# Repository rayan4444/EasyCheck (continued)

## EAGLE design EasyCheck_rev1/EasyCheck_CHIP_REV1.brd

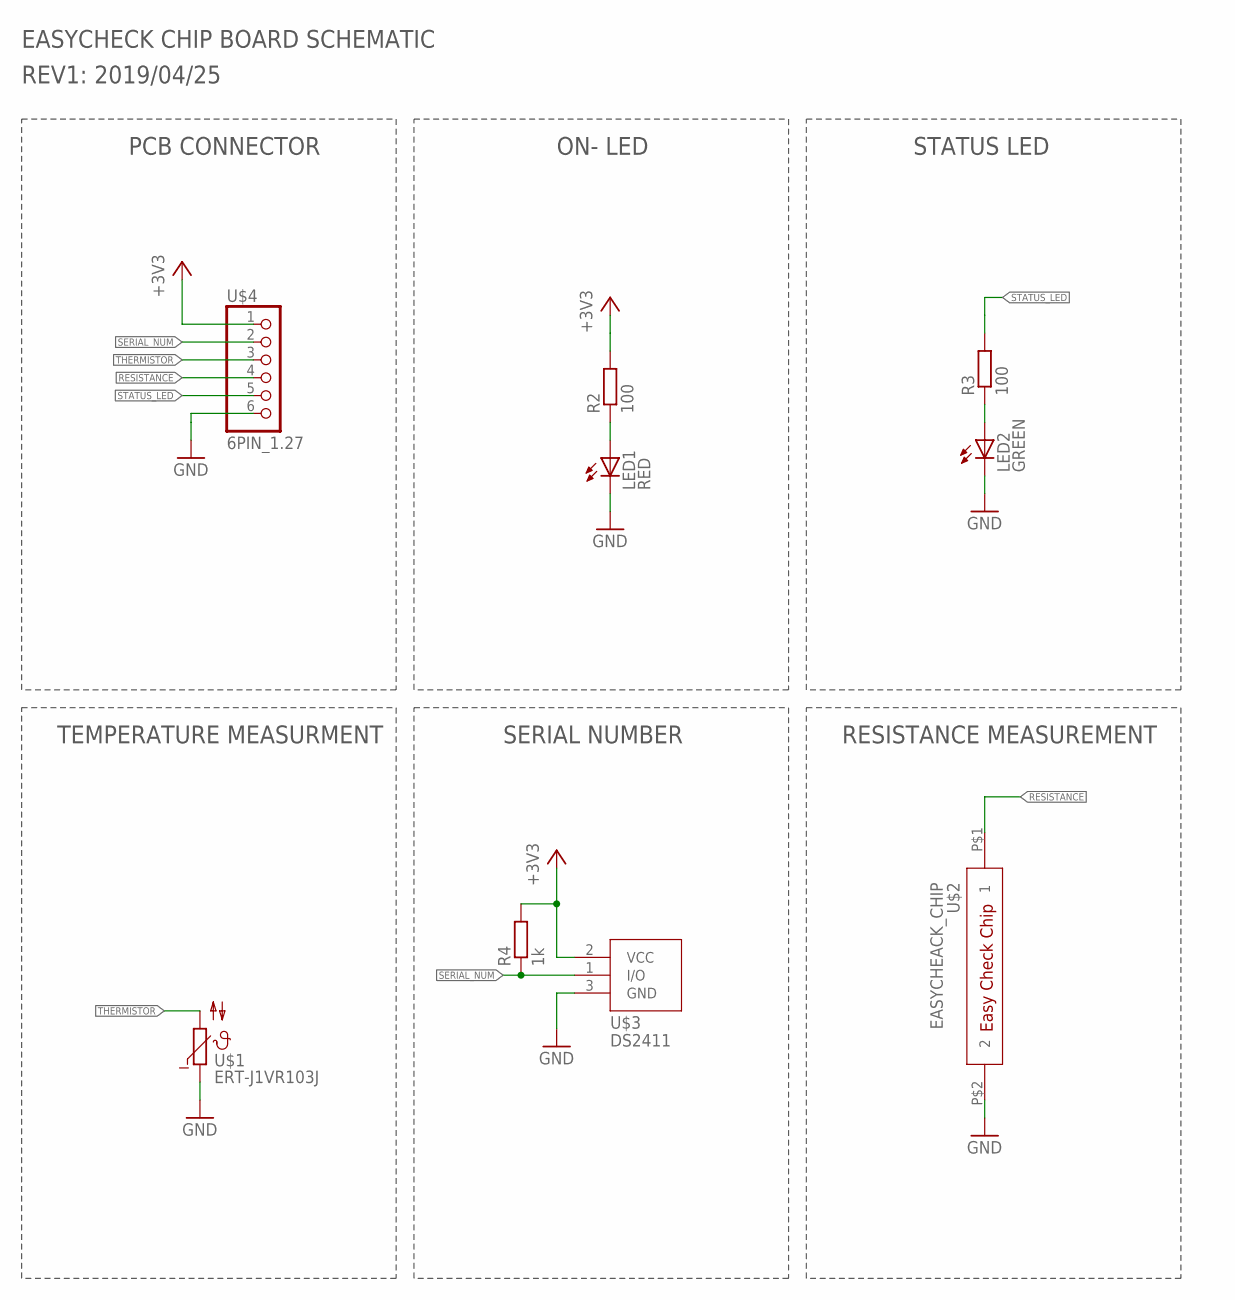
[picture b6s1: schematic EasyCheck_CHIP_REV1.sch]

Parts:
LED1: RED; CHIPLED_0603
LED2: GREEN; CHIPLED_0603
R2, R3: 100; R0402
R4: 1k; R0402
U$1: ERT-J1VR103J; C0603K
U$2: EASYCHEACK_CHIP; EASYCHECK_CHIP
U$3: DS2411; SOT23
U$4: 6PIN_1.27; 6X1PIN_1.27

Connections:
+3V3: R2.2, R4.2, U$3.2 (VCC), U$4.1
GND: LED1.C, LED2.C, U$1.1, U$2.P$2 (2), U$3.3 (GND), U$4.6
unnamed: LED1.A, R2.1
unnamed: LED2.A, R3.1
RESISTANCE: U$2.P$1 (1), U$4.4
SERIAL_NUM: R4.1, U$3.1 (I/O), U$4.2
STATUS_LED: R3.2, U$4.5
THERMISTOR: U$1.2, U$4.3

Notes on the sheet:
EASYCHECK CHIP BOARD SCHEMATIC
REV1: 2019/04/25
PCB CONNECTOR
TEMPERATURE MEASURMENT
ON- LED
STATUS LED
RESISTANCE MEASUREMENT
SERIAL NUMBER

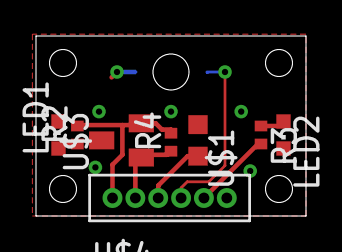
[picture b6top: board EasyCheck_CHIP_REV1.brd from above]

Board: 2 copper layers, 15.0 x 10.0 mm, 9 parts (1 on the bottom side), 8 nets.

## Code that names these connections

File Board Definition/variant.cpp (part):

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 * +------------+------------------+--------+-----------------+--------------------------------------------------------------------------------------------------------
 * |            | Digital Low      |        |                 |
 * +------------+------------------+--------+-----------------+--------------------------------------------------------------------------------------------------------
 * | 0          | 0 -> RX          |  PA11  |                 | EIC/EXTINT[11] ADC/AIN[19]           PTC/X[3] *SERCOM0/PAD[3]  SERCOM2/PAD[3]  TCC0/WO[3]  TCC1/WO[1]
 * | 1          | 1 <- TX          |  PA10  |                 | EIC/EXTINT[10] ADC/AIN[18]           PTC/X[2] *SERCOM0/PAD[2]                  TCC0/WO[2]  TCC1/WO[0]
 * | 2          | 2                |  PA14  |                 | EIC/EXTINT[14]                                 SERCOM2/PAD[2]  SERCOM4/PAD[2]  TC3/WO[0]   TCC0/WO[4]
 * | 3          | ~3               |  PA09  |                 | EIC/EXTINT[9]  ADC/AIN[17]           PTC/X[1]  SERCOM0/PAD[1]  SERCOM2/PAD[1] *TCC0/WO[1]  TCC1/WO[3]
 * | 4          | ~4               |  PA08  |                 | EIC/NMI        ADC/AIN[16]           PTC/X[0]  SERCOM0/PAD[0]  SERCOM2/PAD[0] *TCC0/WO[0]  TCC1/WO[2]
 * | 5          | ~5               |  PA15  |                 | EIC/EXTINT[15]                                 SERCOM2/PAD[3]  SERCOM4/PAD[3] *TC3/WO[1]   TCC0/WO[5]
 * | 6          | ~6               |  PA20  |                 | EIC/EXTINT[4]                        PTC/X[8]  SERCOM5/PAD[2]  SERCOM3/PAD[2]             *TCC0/WO[6]
 * | 7          | 7                |  PA21  |                 | EIC/EXTINT[5]                        PTC/X[9]  SERCOM5/PAD[3]  SERCOM3/PAD[3]              TCC0/WO[7]
 * +------------+------------------+--------+-----------------+--------------------------------------------------------------------------------------------------------
 * |            | Digital High     |        |                 |
 * +------------+------------------+--------+-----------------+--------------------------------------------------------------------------------------------------------
 * | 8          | ~8               |  PA06  |                 | EIC/EXTINT[6]  ADC/AIN[6]  AC/AIN[2] PTC/Y[4]  SERCOM0/PAD[2]                 *TCC1/WO[0]
 * | 9          | ~9               |  PA07  |                 | EIC/EXTINT[7]  ADC/AIN[7]  AC/AIN[3] PTC/Y[5]  SERCOM0/PAD[3]                 *TCC1/WO[1]
 * | 10         | ~10              |  PA18  |                 | EIC/EXTINT[2]                        PTC/X[6] +SERCOM1/PAD[2]  SERCOM3/PAD[2] *TC3/WO[0]    TCC0/WO[2]
 * | 11         | ~11              |  PA16  |                 | EIC/EXTINT[0]                        PTC/X[4] +SERCOM1/PAD[0]  SERCOM3/PAD[0] *TCC2/WO[0]   TCC0/WO[6]
 * | 12         | ~12              |  PA19  |                 | EIC/EXTINT[3]                        PTC/X[7] +SERCOM1/PAD[3]  SERCOM3/PAD[3]  TC3/WO[1]   *TCC0/WO[3]
 * | 13         | ~13              |  PA17  | LED             | EIC/EXTINT[1]                        PTC/X[5] +SERCOM1/PAD[1]  SERCOM3/PAD[1] *TCC2/WO[1]   TCC0/WO[7]
 * +------------+------------------+--------+-----------------+--------------------------------------------------------------------------------------------------------
 * |            | Analog Connector |        |                 |
 * +------------+------------------+--------+-----------------+--------------------------------------------------------------------------------------------------------
 * | 14         | A0               |  PA02  | A0              | EIC/EXTINT[2] *ADC/AIN[0]  DAC/VOUT  PTC/Y[0]
 * | 15         | A1               |  PB08  | A1              | EIC/EXTINT[8] *ADC/AIN[2]            PTC/Y[14] SERCOM4/PAD[0]                  TC4/WO[0]
 * | 16         | A2               |  PB09  | A2              | EIC/EXTINT[9] *ADC/AIN[3]            PTC/Y[15] SERCOM4/PAD[1]                  TC4/WO[1]
 * | 17         | A3               |  PA04  | A3              | EIC/EXTINT[4] *ADC/AIN[4]  AC/AIN[0] PTC/Y[2]  SERCOM0/PAD[0]                  TCC0/WO[0]
 * | 18         | A4               |  PA05  | A4              | EIC/EXTINT[5] *ADC/AIN[5]  AC/AIN[1] PTC/Y[5]  SERCOM0/PAD[1]                  TCC0/WO[1]
 * | 19         | A5               |  PB02  | A5              | EIC/EXTINT[2] *ADC/AIN[10]           PTC/Y[8]  SERCOM5/PAD[0]
 * +------------+------------------+--------+-----------------+--------------------------------------------------------------------------------------------------------
 * |            | Wire             |        |                 |
 * +------------+------------------+--------+-----------------+--------------------------------------------------------------------------------------------------------
 * | 20         | SDA              |  PA22  | SDA             | EIC/EXTINT[6]                        PTC/X[10] *SERCOM3/PAD[0] SERCOM5/PAD[0] TC4/WO[0] TCC0/WO[4]
 * | 21         | SCL              |  PA23  | SCL             | EIC/EXTINT[7]                        PTC/X[11] *SERCOM3/PAD[1] SERCOM5/PAD[1] TC4/WO[1] TCC0/WO[5]
 * +------------+------------------+--------+-----------------+--------------------------------------------------------------------------------------------------------
 * |            |SPI (Legacy ICSP) |        |                 |
 * +------------+------------------+--------+-----------------+--------------------------------------------------------------------------------------------------------
 * | 22         | 1                |  PA12  | MISO            | EIC/EXTINT[12] SERCOM2/PAD[0] *SERCOM4/PAD[0] TCC2/WO[0] TCC0/WO[6]
 * |            | 2                |        | 5V0             |
 * | 23         | 4                |  PB10  | MOSI            | EIC/EXTINT[10]                *SERCOM4/PAD[2] TC5/WO[0]  TCC0/WO[4]
 * | 24         | 3                |  PB11  | SCK             | EIC/EXTINT[11]                *SERCOM4/PAD[3] TC5/WO[1]  TCC0/WO[5]
 * |            | 5                |        | RESET           |
 * |            | 6                |        | GND             |
 * +------------+------------------+--------+-----------------+--------------------------------------------------------------------------------------------------------
 * |            | LEDs             |        |                 |
 * +------------+------------------+--------+-----------------+--------------------------------------------------------------------------------------------------------
 * | 25         |                  |  PB03  | RX              |
 * | 26         |                  |  PA27  | TX              |
 * +------------+------------------+--------+-----------------+--------------------------------------------------------------------------------------------------------
 * |            | USB              |        |                 |
 * +------------+------------------+--------+-----------------+--------------------------------------------------------------------------------------------------------
 * | 27         |                  |  PA28  | USB_HOST_ENABLE | EIC/EXTINT[8]
 * | 28         |                  |  PA24  | USB_NEGATIVE    | *USB/DM
 * | 29         |                  |  PA25  | USB_POSITIVE    | *USB/DP
 * +------------+------------------+--------+-----------------+--------------------------------------------------------------------------------------------------------
 * |            | EDBG             |        |                 |
 * +------------+------------------+--------+-----------------+--------------------------------------------------------------------------------------------------------
 * | 30         |                  |  PB22  | EDBG_UART TX    | *SERCOM5/PAD[2]
 * | 31         |                  |  PB23  | EDBG_UART RX    | *SERCOM5/PAD[3]
 * +------------+------------------+--------+-----------------+--------------------------------------------------------------------------------------------------------
 * | 32         |                  |  PA22  | EDBG_SDA        | Pin 20 (SDA)
 * | 33         |                  |  PA23  | EDBG_SCL        | Pin 21 (SCL)
 * +------------+------------------+--------+-----------------+--------------------------------------------------------------------------------------------------------
 * | 34         |                  |  PA19  | EDBG_MISO       | EIC/EXTINT[3] *SERCOM1/PAD[3] SERCOM3/PAD[3] TC3/WO[1]  TCC0/WO[3]
 * | 35         |                  |  PA16  | EDBG_MOSI       | EIC/EXTINT[0] *SERCOM1/PAD[0] SERCOM3/PAD[0] TCC2/WO[0] TCC0/WO[6]
 * | 36         |                  |  PA18  | EDBG_SS         | EIC/EXTINT[2] *SERCOM1/PAD[2] SERCOM3/PAD[2] TC3/WO[0]  TCC0/WO[2]
 * | 37         |                  |  PA17  | EDBG_SCK        | EIC/EXTINT[1] *SERCOM1/PAD[1] SERCOM3/PAD[1] TCC2/WO[1] TCC0/WO[7]
 * +------------+------------------+--------+-----------------+--------------------------------------------------------------------------------------------------------
 * | 38         | ATN              |  PA13  | EDBG_GPIO0      | EIC/EXTINT[13] SERCOM2/PAD[1] SERCOM4/PAD[1] *TCC2/WO[1] TCC0/WO[7]
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
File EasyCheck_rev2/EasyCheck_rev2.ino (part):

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    //#define DRYING_DURATION 900000 //15 minutes

//pin definitions
#define btn1 19 //PB02
#define btn2 25 //PB03
#define btn3 15 //PB08
#define btn4 30 //PB22
#define buzzer 27 //PA28
#define fan0 8 // pa06
#define fan_speed 16 //pb09
#define heater 11 //PA16

//init device temperature sensor
// #define MB_temp 7 //PA21
// OneWire oneWire(MB_temp);
// DallasTemperature tempSensor(&oneWire);

//pins for LCD Screen
#define TFT_DC 17 //PA04
#define TFT_CS 10 //PA18
#define TFT_MOSI 12 //PA19
#define TFT_MISO 6 //PA20
#define TFT_CLK 13 //PA17
#define TFT_RST 31 //PB23

//create screen object
Adafruit_ILI9341 tft = Adafruit_ILI9341(TFT_CS, TFT_DC, TFT_MOSI, TFT_CLK, TFT_RST, TFT_MISO);
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int servo_angle=35; //change number to tune to correct position

//Serial Number pins
DS2411 ch0(18); //PA05
DS2411 ch1(5); //PA15
DS2411 ch2(2); //PA14
DS2411 ch3(38); //PA13
DS2411 ch4(0); //PA11
DS2411 ch5(1); //PA10
DS2411 ch6(3); //PA09
DS2411 ch7(14); //PA02

//variable to check chip presence
int chip_is_there=0;
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  pinMode(btn2, INPUT);
  pinMode(btn3, INPUT);
  pinMode(btn4, INPUT);
  pinMode(buzzer, OUTPUT); //use tone(buzzer, Freq); and noTone(buzzer) to start and stop sound

  attachInterrupt(digitalPinToInterrupt(btn1), btn1_press, FALLING);
  attachInterrupt(digitalPinToInterrupt(btn2), btn2_press, FALLING);
  attachInterrupt(digitalPinToInterrupt(btn3), btn3_press, FALLING);
  attachInterrupt(digitalPinToInterrupt(btn4), btn4_press, FALLING);

  //servo on PA07, pin9
  servo1.attach(9);

  //setup ADC
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
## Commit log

2019-05-28 Added hardware files, libraries and Test code for Rev1, updated errata in readme
2019-05-31 added BOM
2019-06-18 Added rev2 hardware files
2019-06-18 Added rev 2 BOM
2019-06-18 Created README
2019-07-05 Bug free code so far
    Main working code, everything working separately tested, full test routine not working yet. + README with errata
2019-07-06 full functioning code
    nice to have:
    - modify PID loop to achieve faster results
    - scale plot x axis to duration
    - better alignment of graphics
2019-07-09 Corrected read function
2019-07-09 Added modified board definition files
2019-07-09 Corrected hardware files
